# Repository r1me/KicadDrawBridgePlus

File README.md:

# KicadDrawBridgePlus
PCB design I've made for the DrawBridge Plus! project by Robert Smith. Based on DrawBridge Plus! schematic.
Visit author's page for more information about the project: http://amiga.robsmithdev.co.uk/

3D case: https://www.thingiverse.com/thing:5342990

## Changelog

Rev. 4:
* remove +12V socket, 95% of drives are powered with +5V only
* added pin header for mounting DrawBridge in a PC case (internal USB)

Rev. 3:  
* added floppy power cable relief  
* changed resistors size from 0805 to 1206 for easier assembly  

## FT232 note  
Watch out for fake FT232 chips, buy them only from good known source. With fake chips, a read transfer test will fail, also making disk->SCP read unstable.

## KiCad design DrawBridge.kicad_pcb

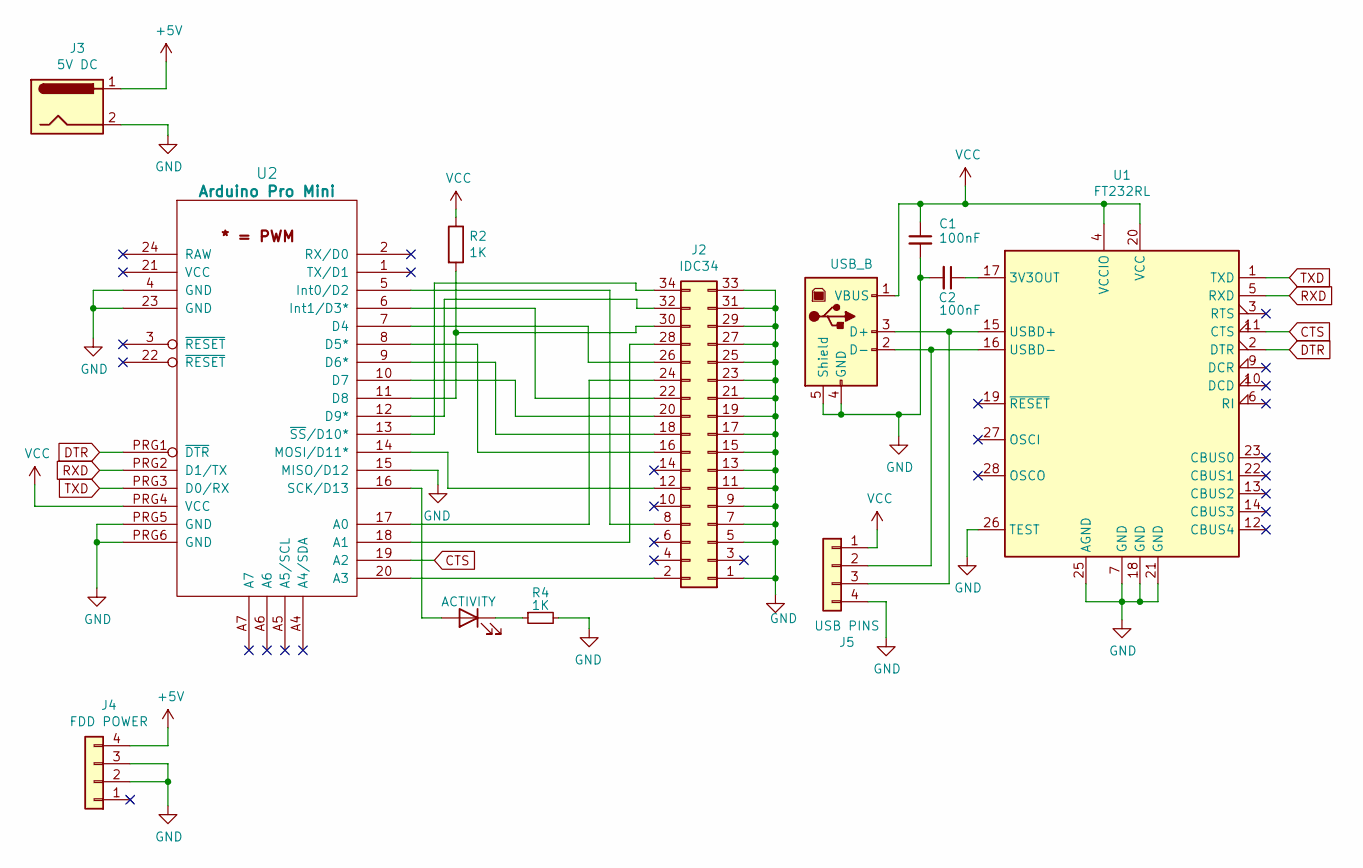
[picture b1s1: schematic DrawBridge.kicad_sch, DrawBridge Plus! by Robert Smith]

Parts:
C1, C2: 100nF; C_1206_3216Metric_Pad1.33x1.80mm_HandSolder
D2: ACTIVITY; LED_D3.0mm_FlatTop
J1: USB_B; USB_B_OST_USB-B1HSxx_Horizontal
J2: IDC34; IDC-Header_2x17_P2.54mm_Vertical
J3: 5V DC; BarrelJack_Wuerth_6941xx301002
J4: FDD POWER; PinHeader_1x04_P2.54mm_Vertical
J5: USB PINS; PinHeader_1x04_P2.54mm_Vertical
R2, R4: 1K; R_1206_3216Metric_Pad1.30x1.75mm_HandSolder
U1: FT232RL; SSOP-28_5.3x10.2mm_P0.65mm
U2: Arduino Pro Mini; ARDUINO_Pro-ADFRW

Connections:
+5V: J3.1, J4.4
CTS: U1.11 (CTS), U2.19 (A2)
DTR: U1.2 (DTR), U2.PRG1 (~DTR)
GND: C1.2, C2.2, J1.4 (GND), J1.5 (Shield), J2.1, J2.5, J2.7, J2.9, J2.11, J2.13, J2.15, J2.17, J2.19, J2.21, J2.23, J2.25, J2.27, J2.29, J2.31, J2.33, J3.2, J4.2, J4.3, J5.4, R4.2, U1.7 (GND), U1.18 (GND), U1.21 (GND), U1.25 (AGND), U1.26 (TEST), U2.4 (GND), U2.15 (MISO/D12), U2.23 (GND), U2.PRG5 (GND), U2.PRG6 (GND)
unnamed: D2.2 (A), U2.16 (SCK/D13)
unnamed: D2.1 (K), R4.1
unnamed: J1.3 (D+), J5.3, U1.15 (USBD+)
unnamed: J1.2 (D-), J5.2, U1.16 (USBD-)
unnamed: J2.2, U2.20 (A3)
unnamed: J2.8, U2.5 (Int0/D2)
unnamed: J2.12, U2.14 (MOSI/D11*)
unnamed: J2.16, U2.8 (D5*)
unnamed: J2.18, U2.9 (D6*)
unnamed: J2.20, U2.10 (D7)
unnamed: J2.22, U2.6 (Int1/D3*)
unnamed: J2.24, U2.17 (A0)
unnamed: J2.26, U2.7 (D4)
unnamed: J2.28, U2.18 (A1)
unnamed: J2.30, R2.2, U2.11 (D8)
unnamed: J2.32, U2.12 (D9*)
unnamed: J2.34, U2.13 (~SS/D10*)
unnamed: C2.1, U1.17 (3V3OUT)
RXD: U1.5 (RXD), U2.PRG2 (D1/TX)
TXD: U1.1 (TXD), U2.PRG3 (D0/RX)
VCC: C1.1, J1.1 (VBUS), J5.1, R2.1, U1.4 (VCCIO), U1.20 (VCC), U2.PRG4 (VCC)

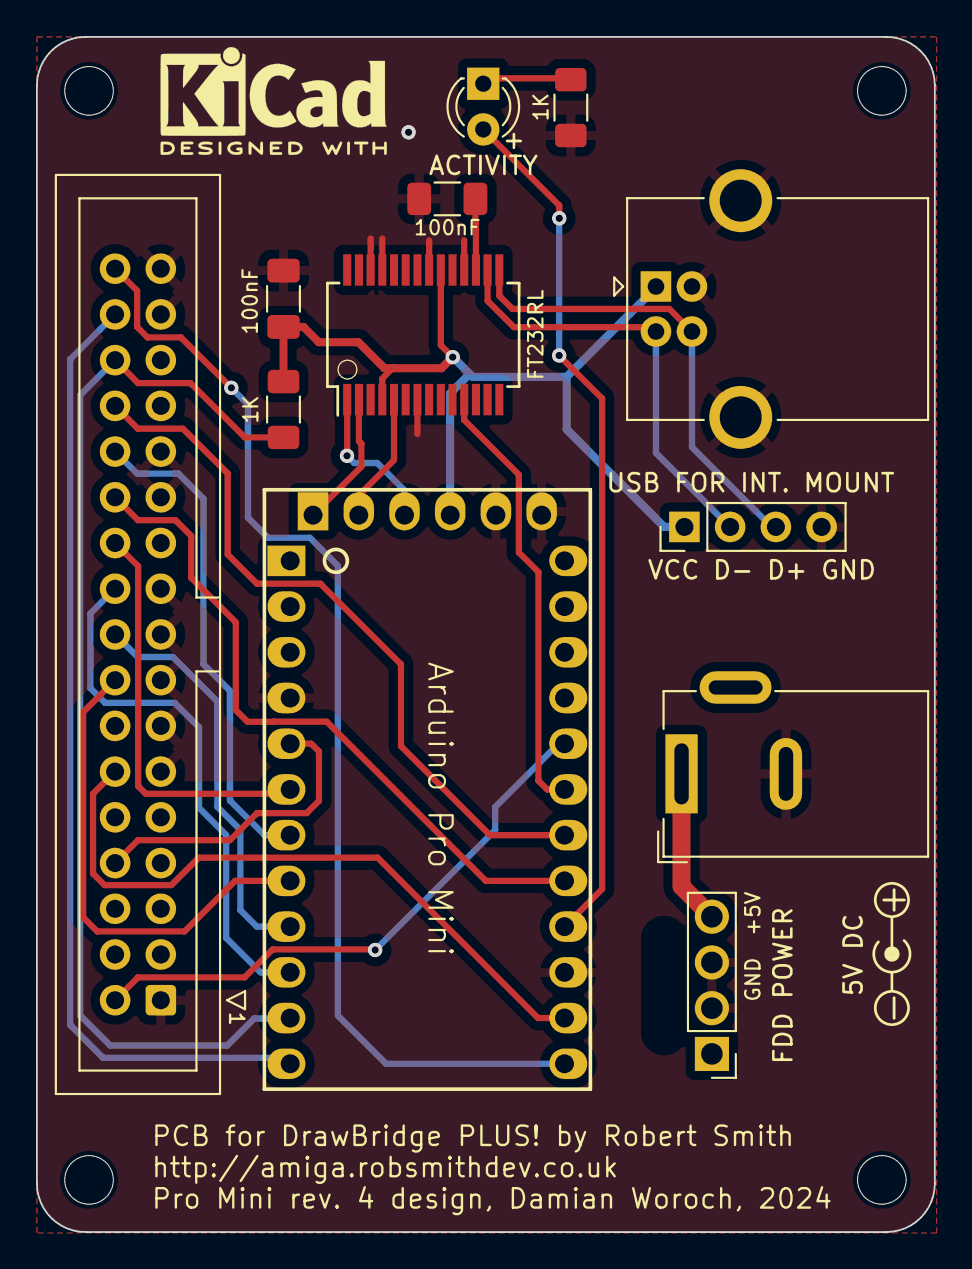
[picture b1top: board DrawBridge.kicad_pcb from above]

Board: 2 copper layers, 49.9 x 66.4 mm, 12 parts (0 on the bottom side), 25 nets.

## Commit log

2022-12-01 Upload project files
2023-01-21 Increase holes for power cable relief
    rev 3b
2024-10-30 Rev 4
